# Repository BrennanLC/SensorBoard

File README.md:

SensorBoard
==============

Line sensor board using the QRE1113 optical sensor.

Design has not yet been verified. Build at your own risk!

Files:

SEN00001.pdf - Copy of board schematic in PDF format

SEN00001.sch - Board schematic eagle file

SEN00001.brd - Board layout eagle file

SEN00001Board.pdf - Board layout in PDF format

schematic and board layout built with Eagle 6.4.0 Standard. More info and 
download available here:

https://www.cadsoftusa.com/

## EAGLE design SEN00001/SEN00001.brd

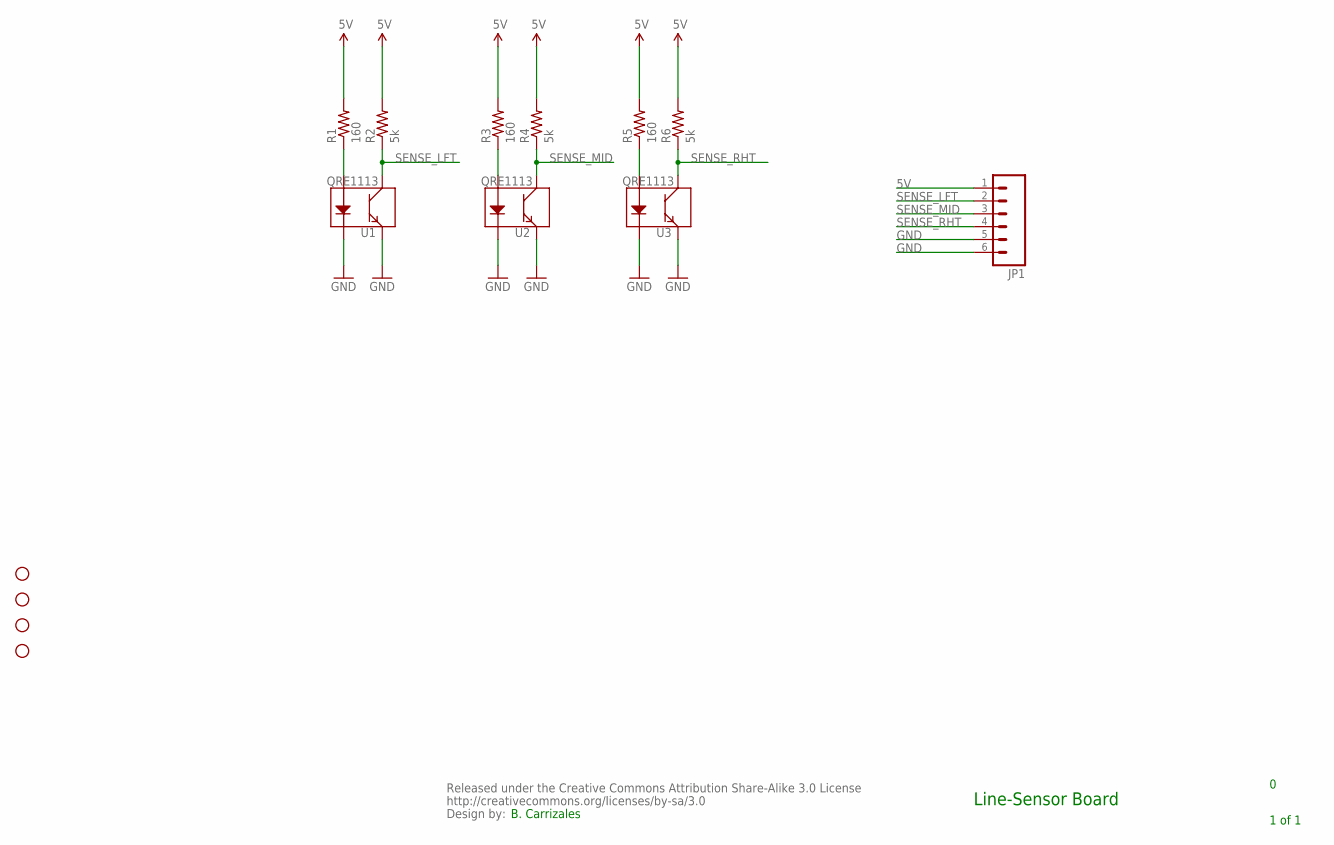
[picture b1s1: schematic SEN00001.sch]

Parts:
CC_TEXT1: CREATIVE_COMMONS
JP1: M06SIP; 1X06
R1, R3, R5: 160; 0603-RES
R2, R4, R6: 5k; 0603-RES
STANDOFF1, STANDOFF2, STANDOFF3, STANDOFF4: STAND-OFF
U1, U2, U3: QRE1113

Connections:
5V: JP1.1, R1.2, R2.2, R3.2, R4.2, R5.2, R6.2
GND: JP1.5, JP1.6, U1.2 (K), U1.4 (E), U2.2 (K), U2.4 (E), U3.2 (K), U3.4 (E)
unnamed: R5.1, U3.1 (A)
unnamed: R3.1, U2.1 (A)
unnamed: R1.1, U1.1 (A)
SENSE_LFT: JP1.2, R2.1, U1.3 (C)
SENSE_MID: JP1.3, R4.1, U2.3 (C)
SENSE_RHT: JP1.4, R6.1, U3.3 (C)

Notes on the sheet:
Line-Sensor Board
1 of 1
B. Carrizales

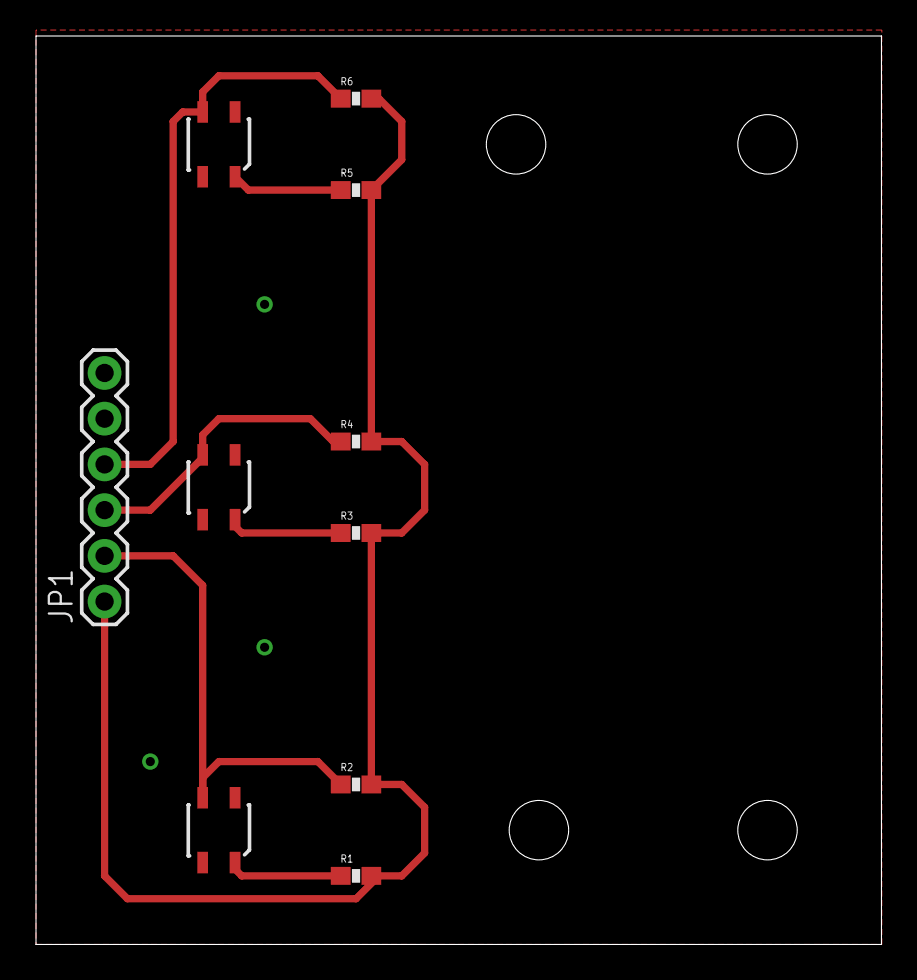
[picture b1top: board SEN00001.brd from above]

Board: 2 copper layers, 47.0 x 50.5 mm, 15 parts (0 on the bottom side), 8 nets.

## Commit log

2014-01-14 Finished Major Layout
    Finished schematic and finished major layout. Created BOM
2014-02-20 Updated Description
    Updated layout and schematic. Updated readme file and added pdf versions
    of the schematic and board

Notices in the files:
parts and their libraries:
SparkFun-Sensors: Licensing: CC v3.0 Share-Alike You are welcome to use this library for commercial purposes.
SparkFun-Aesthetics: Released under the Creative Commons Attribution Share-Alike 3.0 License
SparkFun-Aesthetics: http://creativecommons.org/licenses/by-sa/3.0
